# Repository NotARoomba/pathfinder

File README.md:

# Tutorial Pathfinder

## Pathfinder Session 1 - 38 minutes

Hice la esquematica.

## Pathfinder Session 2 - 50 minutes

Termine el PCB y estoy instalando Arduino IDE.

## Pathfinder Session 3 - 20 minutes

Termine de instalar Arduino IDE y termine el codigo.

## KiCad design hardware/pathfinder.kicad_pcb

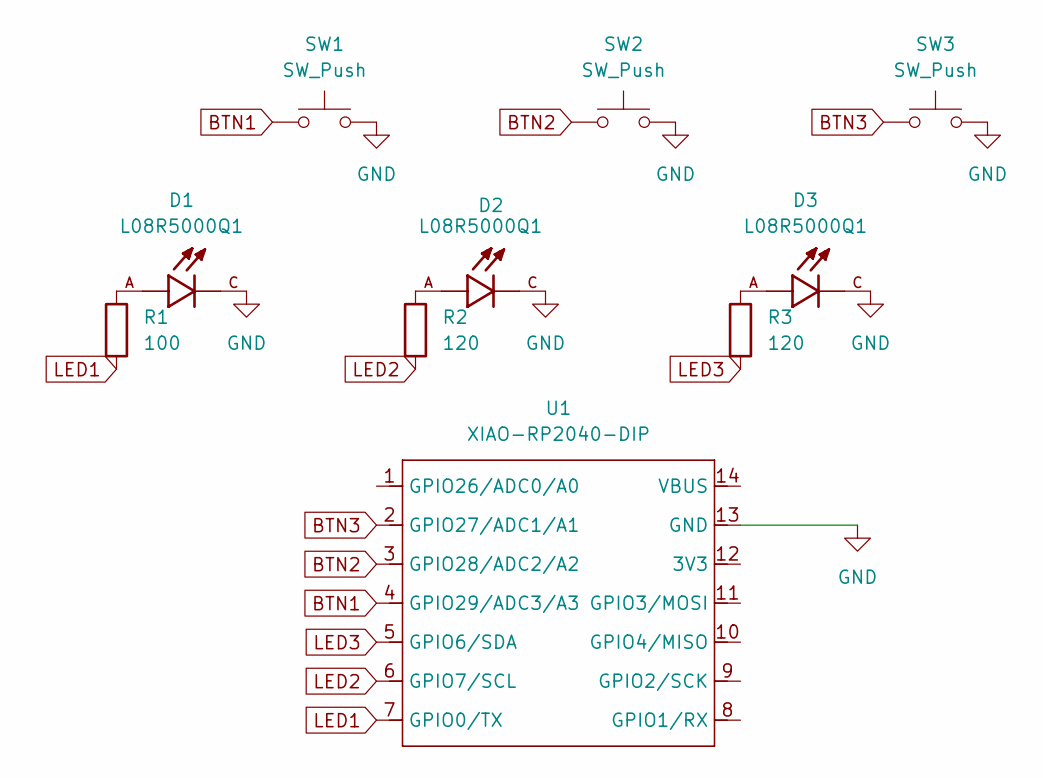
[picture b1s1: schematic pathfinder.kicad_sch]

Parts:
D1, D2, D3: L08R5000Q1; LEDRD254W57D500H1070; PARTREV NA
R1: 100; R_Axial_DIN0204_L3.6mm_D1.6mm_P5.08mm_Horizontal
R2, R3: 120; R_Axial_DIN0204_L3.6mm_D1.6mm_P5.08mm_Horizontal
SW1, SW2, SW3: SW_Push; SW_Cherry_MX_1.00u_PCB
U1: XIAO-RP2040-DIP

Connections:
BTN1: SW1.1, U1.4 (GPIO29/ADC3/A3)
BTN2: SW2.1, U1.3 (GPIO28/ADC2/A2)
BTN3: SW3.1, U1.2 (GPIO27/ADC1/A1)
GND: D1.C, D2.C, D3.C, SW1.2, SW2.2, SW3.2, U1.13 (GND)
LED1: R1.2, U1.7 (GPIO0/TX)
LED2: R2.2, U1.6 (GPIO7/SCL)
LED3: R3.2, U1.5 (GPIO6/SDA)
unnamed: D1.A, R1.1
unnamed: D2.A, R2.1
unnamed: D3.A, R3.1

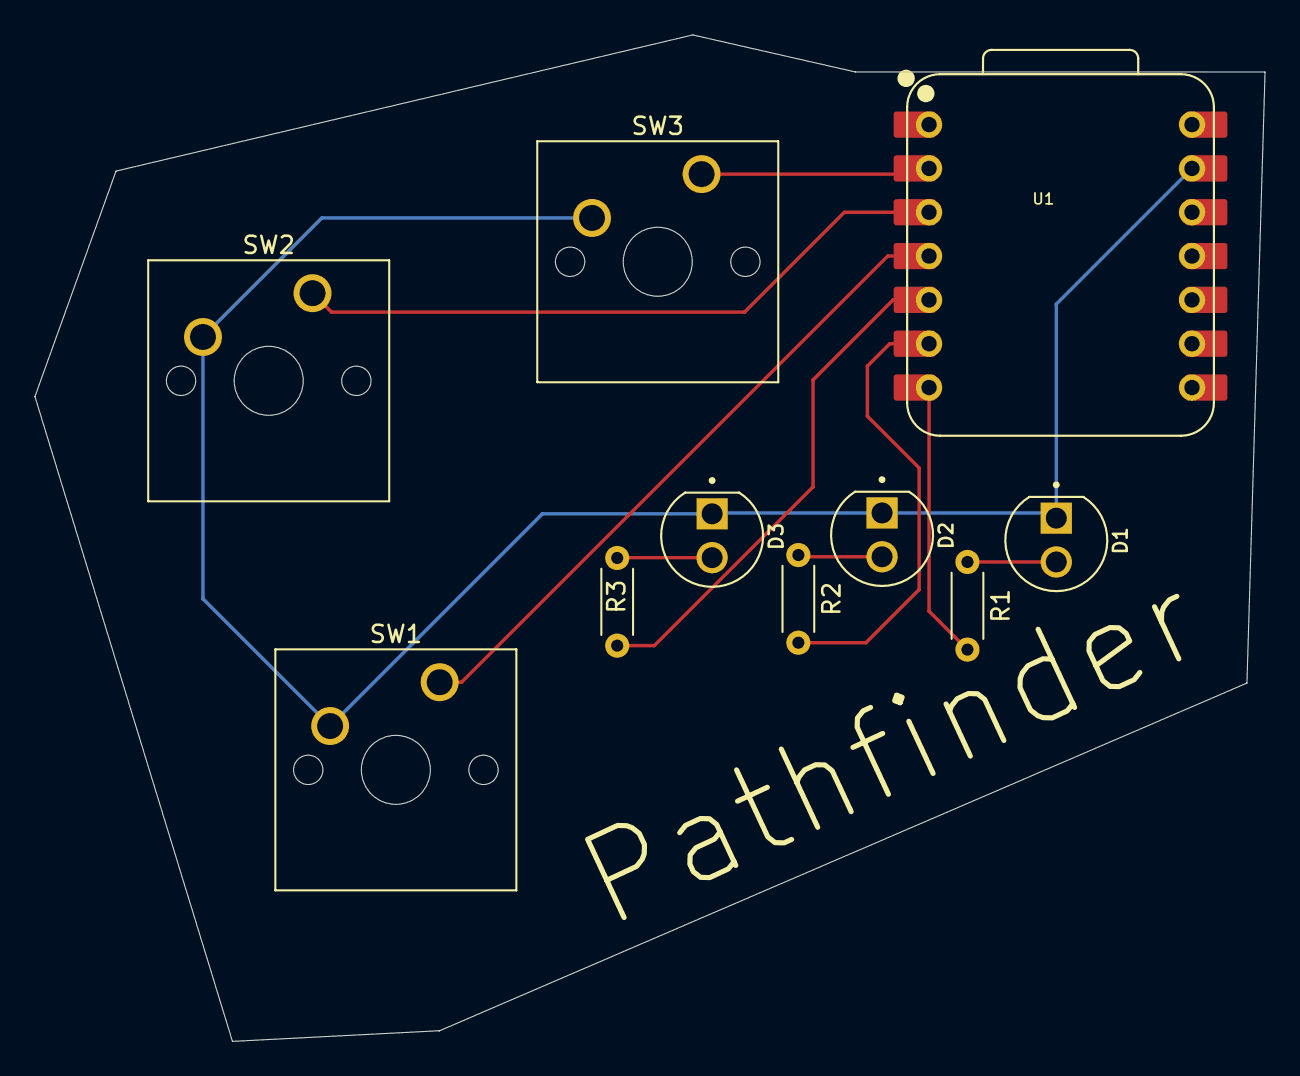
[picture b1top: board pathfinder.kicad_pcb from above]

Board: 2 copper layers, 71.3 x 58.3 mm, 10 parts (0 on the bottom side), 10 nets.

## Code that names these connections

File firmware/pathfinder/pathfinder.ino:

int BTN1 = D29;
int BTN2 = D28;
int BTN3 = D27;

int LED1 = D0;
int LED2 = D7;
int LED3 = D6;


void setup() {
  // put your setup code here, to run once:
  pinMode(BTN1, INPUT_PULLUP);
  pinMode(BTN2, INPUT_PULLUP);
  pinMode(BTN3, INPUT_PULLUP);

  pinMode(LED1, OUTPUT);
  pinMode(LED2, OUTPUT);
  pinMode(LED3, OUTPUT);

  long startTime = millis();
}

void loop() {
  // put your main code here, to run repeatedly:
  long btn1time = 0;
  long btn2time = 0;
  long btn3time = 0;

  if (digitalRead(BTN1) == HIGH) {
    btn1time = millis();
    digitalWrite(LED1, HIGH);
  } else {
    digitalwrite(LED1, LOW);
  }
  if (digitalRead(BTN2) == HIGH) {
    btn2time = millis();
  }

  if (abs(btn2time - btn1time) <= 2000) {
    digitalWrite(LED2, HIGH);
  } else {
    digitalwrite(LED2, LOW);
  }

   if (digitalRead(BTN3) == HIGH) {
    btn3time = btn3time + 1; 
    // btn3time +=1;
    // btn3time++;

  } else {
    btn3time = 0;
  }


  if (btn3time >= 800) {
    digitalWrite(LED3, HIGH);
  } else {
    digitalwrite(LED3, LOW);
  }
}

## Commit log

2025-10-26 esquematica
2025-10-26 Add README with tutorial session details
2025-10-26 finish pcb
2025-10-26 Update README with Pathfinder Session 2 details
    Added details for Pathfinder Session 2 and updated PCB installation status.
2025-10-26 Update README with Arduino IDE installation details
    Added updates about Arduino IDE installation and code completion.
2025-10-26 production files
